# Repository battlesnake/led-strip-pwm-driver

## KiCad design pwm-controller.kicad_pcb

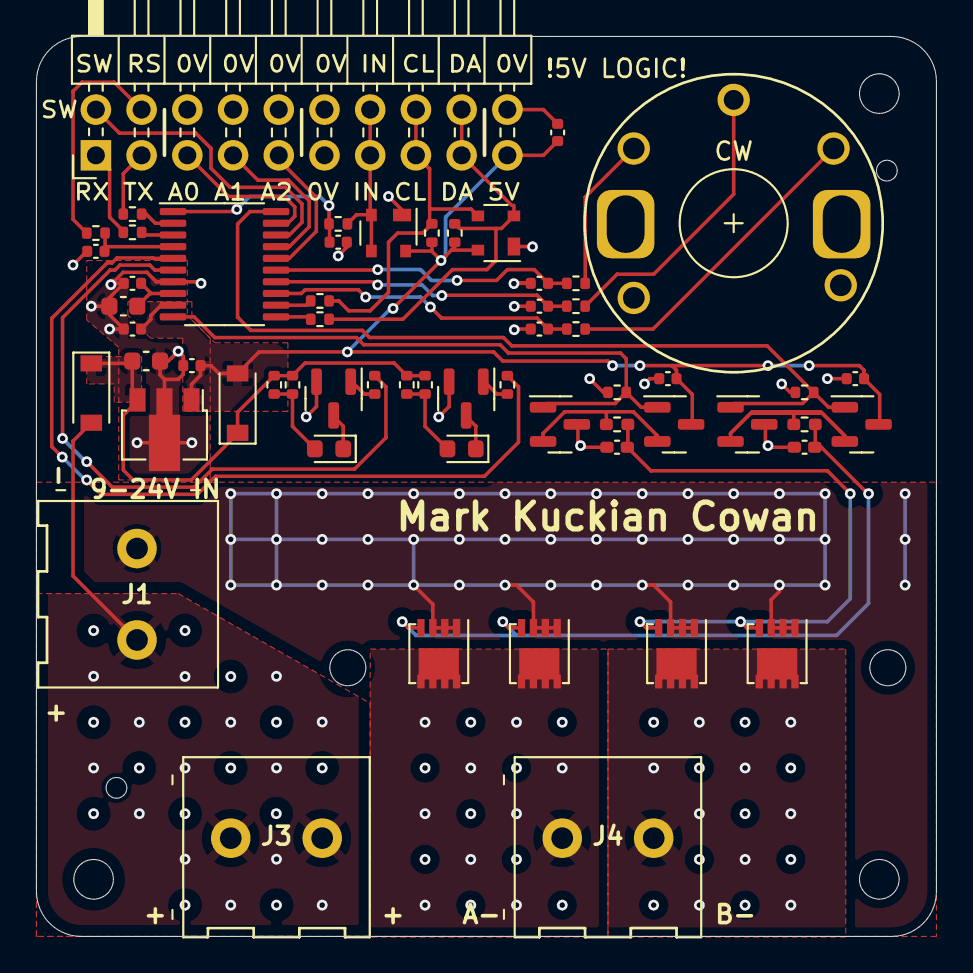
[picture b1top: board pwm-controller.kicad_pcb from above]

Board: 4 copper layers, 50.0 x 50.0 mm, 67 parts (1 on the bottom side), 43 nets.

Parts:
C1, C11: 1u/50; C_0603_1608Metric
C2, C3, C4, C5, C6, C7, C8, C9, C10, C12, C14: 100n; C_0402_1005Metric
C13, C15: 100n; C_0402_1005Metric_Pad0.74x0.62mm_HandSolder
D1, D2: B5819W SL; D_SOD-123
D3: Blue; LED_0603_1608Metric
D4: Green; LED_0603_1608Metric
G1: Roger; roger
H1, H2: JLC; JLCPCB_ToolingHole_1152_1300_1400_1650
H3, H4, H5: M2; MountingHole_2.2mm_M2
H6, H7: M2; MountingHole_2mm
J1: POWER; ScrewTerminal_5.08P_1x02_10.16x10.16mm
J2: DEBUG_ADDRESS_I2C_INT_5V; PinHeader_2x10_P2.54mm_Horizontal
J3: OUT+; ScrewTerminal_5.08P_1x02_10.16x10.16mm
J4: OUT-; ScrewTerminal_5.08P_1x02_10.16x10.16mm
Q1, Q5, Q9, Q10: MMBT5551; SOT-23
Q2, Q6: MMBT5401; SOT-23
Q3, Q4, Q7, Q8: SiS402DN; Vishay_PowerPAK_1212-8_Single
R1, R2, R5, R6, R7, R8, R9, R10, R11: 100; R_0402_1005Metric
R3, R4, R12, R14, R16, R17, R18, R19, R20, R21: 4.7k; R_0402_1005Metric
R13, R15: 100; R_0402_1005Metric_Pad0.72x0.64mm_HandSolder
SW1: EC12D1524403; RotaryEncoder_Alps_EC12D_Vertical_H20mm_easy
U1: 78L05; SOT-89-3
U2: STM8S003F3Px; TSSOP-20_4.4x6.5mm_P0.65mm
U3, U4: DRTR5V0U2SR; SOT-143

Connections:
+5V: C2.1, C7.1, C8.2, C12.1, C14.1, D2.2 (A), J2.19, Q1.3 (C), Q5.3 (C), R3.2, R4.2, U1.1 (OUT), U2.9 (VDD), U3.4 (VCC), U4.4 (VCC)
/INT_PIN: C3.2, R8.2, U2.1 (PD4/INT)
/NRST_PIN: C10.1, R11.2, U2.4 (NRST)
/SCL_PIN: R6.2, U2.12 (PB4/SCL)
/SDA_PIN: R7.2, U2.11 (PB5/SDA)
/URX_PIN: R10.2, U2.3 (PD6/URX)
/UTX_PIN: R9.2, U2.2 (PD5/UTX)
/VCAP: C9.2, C11.1, U2.8 (VCAP)
/channel1/GATE: C13.1, Q3.4 (G), Q4.4 (G), R13.2
/channel2/GATE: C15.1, Q7.4 (G), Q8.4 (G), R15.2
/led_driver1/LED_A: D4.2 (A), R16.2, R17.2
/led_driver1/LED_K: D4.1 (K), Q9.3 (C)
/led_driver2/LED_A: D3.2 (A), R19.2, R20.2
/led_driver2/LED_K: D3.1 (K), Q10.3 (C)
DRAIN1: J4.2, Q3.5 (D), Q4.5 (D)
DRAIN2: J4.1, Q7.5 (D), Q8.5 (D)
GND: C1.2, C2.2, C3.1, C4.1, C5.1, C6.1, C7.2, C8.1, C9.1, C10.2, C11.2, C12.2, C13.2, C14.2, C15.2, J1.1, J2.6, J2.8, J2.10, J2.11, J2.12, J2.20, Q2.3 (C), Q3.1 (S), Q3.2 (S), Q3.3 (S), Q4.1 (S), Q4.2 (S), Q4.3 (S), Q6.3 (C), Q7.1 (S), Q7.2 (S), Q7.3 (S), Q8.1 (S), Q8.2 (S), Q8.3 (S), Q9.2 (E), Q10.2 (E), R12.2, R14.2, SW1.C, SW1.S2, U1.2 (GND), U2.7 (VSS), U3.1 (GND), U4.1 (GND)
INT: J2.13, J2.14, R8.1, U4.2 (A), U4.3 (B)
LED1: R21.2, U2.5 (PA1/LED1)
LED2: R18.2, U2.6 (PA2/LED2)
NRST: J2.4, R11.1
unnamed: Q1.2 (E), Q2.2 (E), R13.1
unnamed: Q5.2 (E), Q6.2 (E), R15.1
unnamed: Q9.1 (B), R18.1
unnamed: Q10.1 (B), R21.1
unnamed: R1.1, SW1.A
unnamed: R2.1, SW1.B
unnamed: R5.2, SW1.S1
PWM1: Q1.1 (B), Q2.1 (B), R12.1, U2.10 (PA3/PWM1)
PWM2: Q5.1 (B), Q6.1 (B), R14.1, U2.20 (PD3/PWM2)
RE_B: C6.2, R5.1, U2.14 (PC4/RE_B)
RE_I: C4.2, R1.2, U2.15 (PC5/RE_I)
RE_Q: C5.2, R2.2, U2.13 (PC3/RE_Q)
SADD0: J2.5, U2.19 (PD2/SADD0)
SADD1: J2.7, U2.17 (PC7/SADD1)
SADD2: J2.9, U2.16 (PC6/SADD2)
SCL: J2.15, J2.16, R3.1, R6.1, U3.3 (B)
SDA: J2.17, J2.18, R4.1, R7.1, U3.2 (A)
SWIM: J2.2, U2.18 (PD1/SWIM)
URX: J2.1, R10.1
UTX: J2.3, R9.1
VIN: D1.2 (A), J1.2, J3.1, J3.2
VIN_D: C1.1, D1.1 (K), D2.1 (K), R16.1, R17.1, R19.1, R20.1, U1.3 (IN)

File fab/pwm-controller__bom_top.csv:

"Comment","Designator","Footprint","LCSC Part Number"
"EC12D1524403","SW1","RotaryEncoder_Alps_EC12D_Vertical_H20mm_easy","C112349"
"100n","C10 C12 C13 C14 C15 C2 C3 C4 C5 C6 C7 C8 C9","0402","C1525"
"SiS402DN","Q3 Q4 Q7 Q8","Vishay_PowerPAK_1212-8_Single","C15791"
"1u/50","C1 C11","0603","C15849"
"MMBT5551","Q1 Q10 Q5 Q9","SOT-23","C2145"
"100","R1 R10 R11 R13 R15 R2 R5 R6 R7 R8 R9","0402","C25076"
"4.7k","R12 R14 R16 R17 R18 R19 R20 R21 R3 R4","0402","C25900"
"DEBUG_ADDRESS_I2C_INT_5V","J2","PinHeader_2x10_P2.54mm_Horizontal","C492438"
"STM8S003F3Px","U2","TSSOP-20_4.4x6.5mm_P0.65mm","C52717"
"78L05","U1","SOT-89-3","C71136"
"Blue","D3","0603","C72041"
"Green","D4","0603","C72043"
"MMBT5401","Q2 Q6","SOT-23","C8326"
"OUT+ OUT- POWER","J1 J3 J4","ScrewTerminal_5.08P_1x02_10.16x10.16mm","C8465"
"B5819W SL","D1 D2","D_SOD-123","C8598"

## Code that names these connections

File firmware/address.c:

#include <stm8s.h>

#define PIN_SADD0 GPIOD, GPIO_PIN_2
#define PIN_SADD1 GPIOC, GPIO_PIN_7
#define PIN_SADD2 GPIOC, GPIO_PIN_6

unsigned char address;

void address_setup(unsigned char base)
{
	/* A3, D3 = PWM1, PWM2 */
	GPIO_Init(PIN_SADD0, GPIO_MODE_IN_PU_NO_IT);
	GPIO_Init(PIN_SADD1, GPIO_MODE_IN_PU_NO_IT);
	GPIO_Init(PIN_SADD2, GPIO_MODE_IN_PU_NO_IT);

	bool addr0 = GPIO_ReadInputPin(PIN_SADD0);
	bool addr1 = GPIO_ReadInputPin(PIN_SADD1);
	bool addr2 = GPIO_ReadInputPin(PIN_SADD2);

	address = base | (addr2 ? 0 : 4) | (addr1 ? 0 : 2) | (addr0 ? 0 : 1);
}

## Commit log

2021-12-09 initial
2021-12-19 ready, but some cost-saving opportunities left
2021-12-19 dual channel, cheaper (jellybean gate driver)
2021-12-22 simulation provided many improvements, now aboutto switch to 5v single-rail for all control stuff
2021-12-23 sim works nicely with 3 fets @ 5A, hits >100°C for 10A. will change mosfet.
2021-12-23 lets try a single irlr7843 instead
2021-12-23 sim with irlr7843
2021-12-27 b-field study
2021-12-27 happy with driver design, migrate back to schematic
2021-12-28 ready?
2021-12-28 about to remove most pullups (use internals instead) and reroute IOs
2021-12-29 ready to order?
2021-12-29 moved screw terminals to edge of board, reduced stitching/thermal-via frequency
2021-12-29 we can tolerate higher frequencies as long as our led strips are only a dozen or so metres long
2021-12-29 add mosfets, fix led+i2c resistors
2021-12-30 going to swap LEDs and 5V supply over in layout
2021-12-30 swapped placement for 5V LDO vs LEDs, for more stable 5V supply when power-side of ground is noisy
2021-12-31 order ready
2021-12-31 exposed NRST
2021-12-31 minor silkscreen fix
2022-01-01 added some fills
2022-01-01 Fixed VCAP (3.3nF should be 470...3300nF)
2022-01-02 migrated to Kicad v6, fixed a bunch of DRC issues
2022-01-04 order files
2022-03-20 start of firmware project
2022-03-20 SPL source
2022-03-20 rendered some docs
2022-03-29 stlink/stm8 pdfs
2022-03-29 flash as ELF
2022-03-31 gdb and flashing LEDs achieved
2022-03-31 failed to read GPIOs from switch, as switch footprint is probably wrong
2022-03-31 BUG added regarding switch footprint
2022-04-01 serial attempt, no success yet
2022-04-01 random kicad view stuff
2022-04-02 serial working both ways, rx queue interrupt-driven (overrun check not tested yet)
2022-04-08 fix rotary pinout, add 5v0 to header in extra-col, regen fab+doc
2022-04-08 general ringbuffer template, UART TX driven by interrupts now
2022-04-08 TIM1 configured for 1ms ticks, 1000ms LED heartbeat to confirm
2022-04-08 rename uart->serial
2022-04-08 removed broken symlink for SPL exmaples
2022-04-08 gpio split into rotary/led units
2022-04-08 basic string builder added
2022-04-09 basic CLI with vim-style navigation
2022-04-09 pre-cleanup
2022-04-10 led timed flash, %c bugfix, cli works for getting/setting PWM duty %
2022-04-11 both PWMs work (wrong channel used before)
2022-04-13 cleanup
2022-04-13 "pwm cycle <fast|medium|slow>" command added and works
2022-04-14 TVS diodes added to I2C SDA+SCL+INT pins, renamed 1-/2- to A-/B-
2022-04-14 added pdf for TVS diodes
2022-04-27 serial-cli added, not integrated yet
2022-05-08 new CLI (serial_cli) integrated and tested briefly
2022-05-08 toolchain committed
2022-05-08 address: reads address from GPIOs at startup, also 32-point sine added
2022-05-19 improvements, notes for future TODO stuff
2022-08-02 str.c/h moved to u-lib
